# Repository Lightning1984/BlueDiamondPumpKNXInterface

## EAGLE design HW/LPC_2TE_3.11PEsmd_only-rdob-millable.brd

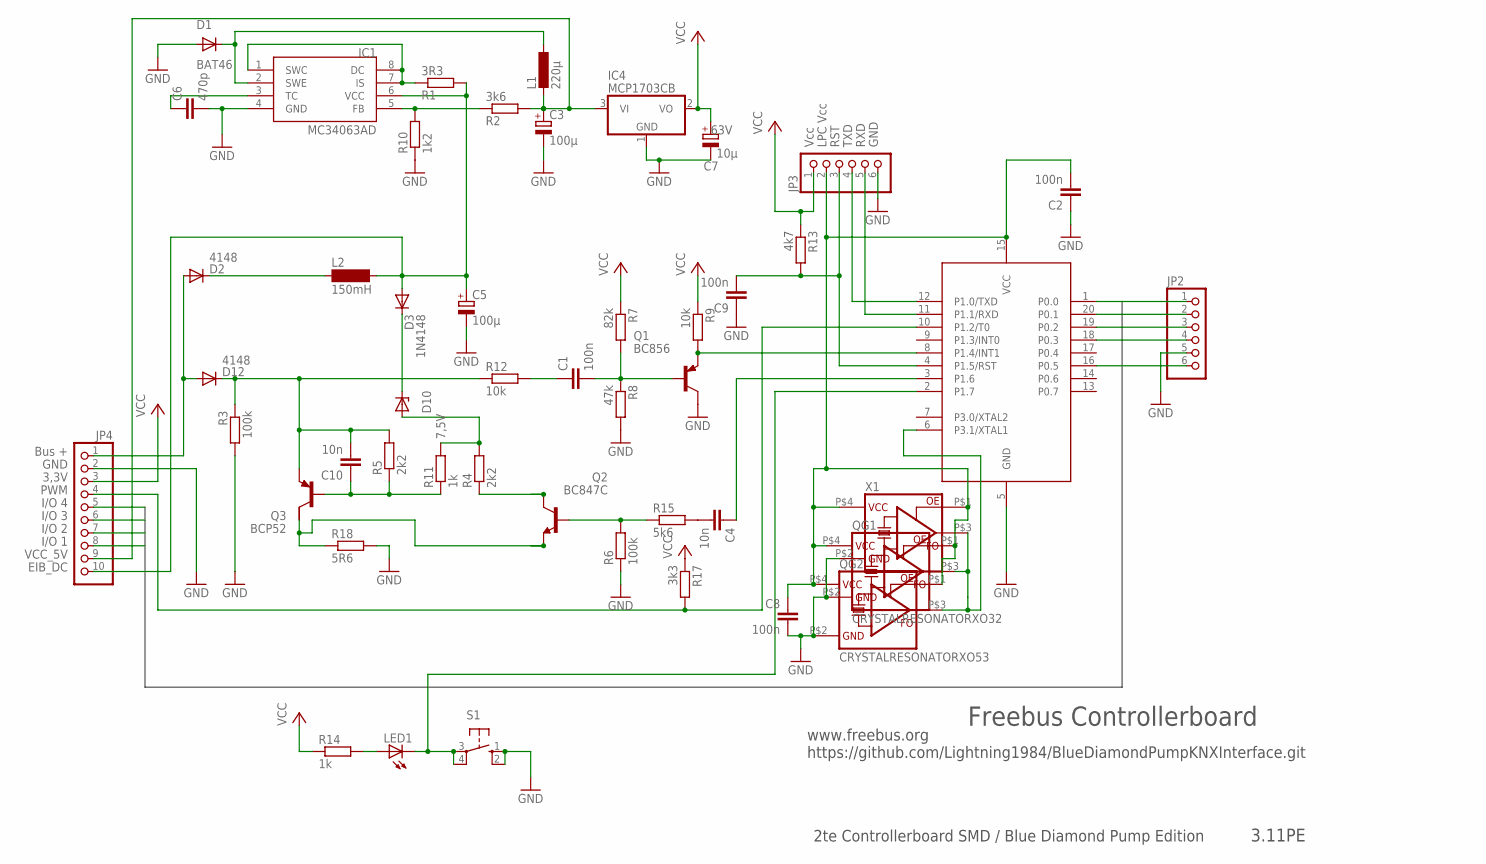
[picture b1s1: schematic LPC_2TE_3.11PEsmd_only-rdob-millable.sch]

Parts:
C1, C2, C8, C9: 100n; C0805K
C3: 100µ; E2,5-6
C4, C10: 10n; C0805K
C5: 100µ; E3,5-8
C6: 470p; C0805K
C7: 10µ; E2-5; VOLTAGE 63V
D1: BAT46; SOD-123
D2, D12: 4148; MINIMELF
D3: 1N4148; MINIMELF
D10: 7,5V; MINIMELF
IC1: MC34063AD; SOIC8
IC2: LPC922FDH; TSSOP20
IC4: MCP1703CB; SOT23
JP2: PINHD-1X06_2.54-0.70MM-DRILL; 1X06-0.70DRILL
JP3: PINHD-1X06_2.54-0.90MM-DRILL; 1X06-0.90DRILL
JP4: PINHD-1X10_2.54-S0.70MM-DRILL; 1X10-0.70DRILL
L1: 220µ; PIS28XX
L2: 150mH; BS11
LED1: LEDSMT1206; 1206
Q1: BC856; SOT23-BEC
Q2: BC847C; SOT23
Q3: BCP52; SOT223
QG1: CRYSTALRESONATORXO32; XO32
QG2: CRYSTALRESONATORXO53; XO53
R1: 3R3; R1206
R2: 3k6; R1206
R3, R6: 100k; R1206
R4, R5: 2k2; R1206
R7: 82k; R1206
R8: 47k; R1206
R9, R12: 10k; R1206
R10: 1k2; R1206
R11, R14: 1k; R1206
R13: 4k7; R1206
R15: 5k6; R1206
R17: 3k3; R1206
R18: 5R6; R1206
S1: 10-XX; B3F-10XX
X1: CRYSTALRESONATORXO91; XO91

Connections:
/RESET: C9.2, IC2.4 (P1.5/RST), JP3.3, R13.2
BASE: C1.2, Q1.B, R7.2, R8.1
BASE_SEND: Q2.1 (B), R6.2, R15.1
EIB+: D2.A, D12.A, JP4.1
EIB_DC: C5.+, D3.A, IC1.6 (VCC), JP4.10, L2.2, R1.2
FEEDBACK: IC1.5 (FB), R2.1, R10.2
GND: C2.1, C3.-, C5.-, C6.2, C7.-, C8.2, C9.1, D1.A, IC1.4 (GND), IC2.5 (GND), IC4.1 (GND), JP2.5, JP3.6, JP4.2, Q1.C, QG1.P$2 (GND), QG2.P$2 (GND), R3.2, R6.1, R8.2, R10.1, R18.2, S1.1 (S), S1.2 (S1), X1.P$2 (GND)
I_SENSE: Q2.2 (E), Q3.2 (C), R18.1
unnamed: Q2.3 (C), R4.1
unnamed: C10.2, D12.C, Q3.3 (E), R3.1, R5.2, R12.1
unnamed: IC2.6 (P3.1/XTAL1), QG1.P$3 (FO), QG2.P$3 (FO), X1.P$3 (FO)
unnamed: IC1.1 (SWC), IC1.7 (IS), IC1.8 (DC), R1.1
unnamed: LED1.A, R14.2
unnamed: D2.C, L2.1
unnamed: C6.1, IC1.3 (TC)
unnamed: D3.C, D10.C
unnamed: C1.1, R12.2
unnamed: C4.2, R15.2
unnamed: C10.1, Q3.1 (B), R5.1, R11.1
P0.0: IC2.1 (P0.0), JP2.1, JP4.8
P0.1: IC2.20 (P0.1), JP2.2, JP4.7
P0.2: IC2.19 (P0.2), JP2.3, JP4.6
P0.3: IC2.18 (P0.3), JP2.4, JP4.5
P0.5: IC2.16 (P0.5), JP2.6
PROG: IC2.2 (P1.7), LED1.C, S1.3, S1.4 (P1)
PWM: IC2.10 (P1.2/T0), JP4.4, R17.2
REFERENZ: D10.A, R4.2, R11.2
RXD: IC2.11 (P1.1/RXD), JP3.5
SIGIN: IC2.8 (P1.4/INT1), Q1.E, R9.2
SIGOUT: C4.1, IC2.3 (P1.6)
SWITCHED: D1.C, IC1.2 (SWE), L1.2 (1)
TXD: IC2.12 (P1.0/TXD), JP3.4
VCC: C7.+, IC4.2 (VO), JP3.1, JP4.3, R7.1, R9.1, R13.1, R14.1, R17.1
VCC_5V: C3.+, IC4.3 (VI), JP4.9, L1.1 (2), R2.2
VCC_LPC: C2.2, C8.1, IC2.15 (VCC), JP3.2, QG1.P$1 (OE), QG1.P$4 (VCC), QG2.P$1 (OE), QG2.P$4 (VCC), X1.P$1 (OE), X1.P$4 (VCC)

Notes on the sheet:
Bus +
GND
3,3V
PWM
I/O 1
I/O 2
I/O 3
I/O 4
Vcc
LPC Vcc
RST
TXD
RXD
VCC_5V
Freebus Controllerboard
www.freebus.org https://github.com/Lightning1984/BlueDiamondPumpKNXInterface.git
2te Controllerboard SMD / Blue Diamond Pump Edition
3.11PE
EIB_DC

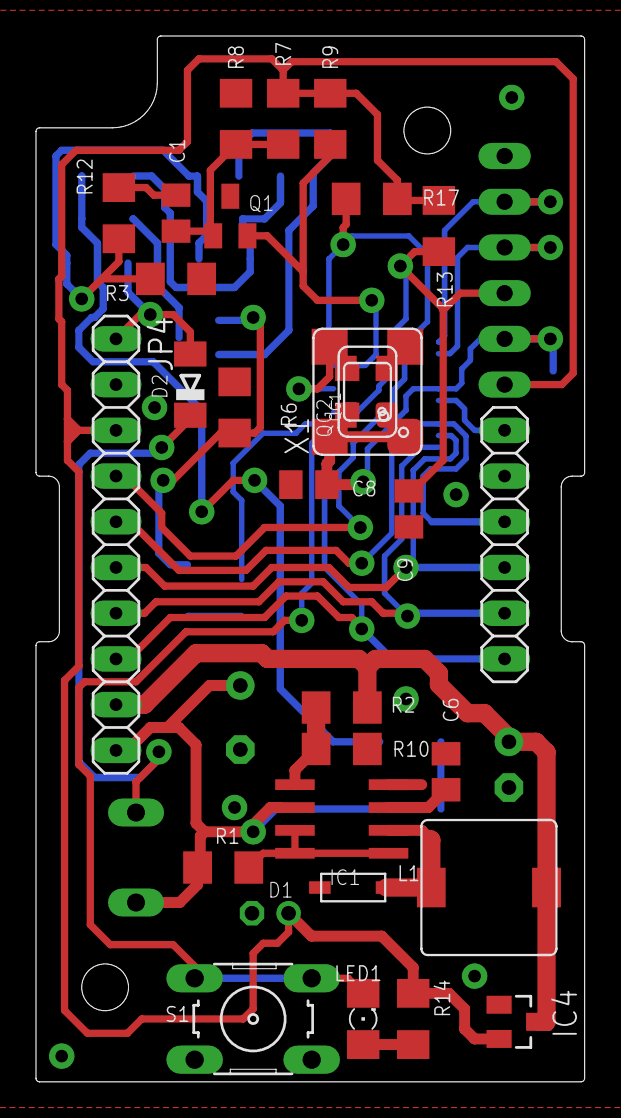
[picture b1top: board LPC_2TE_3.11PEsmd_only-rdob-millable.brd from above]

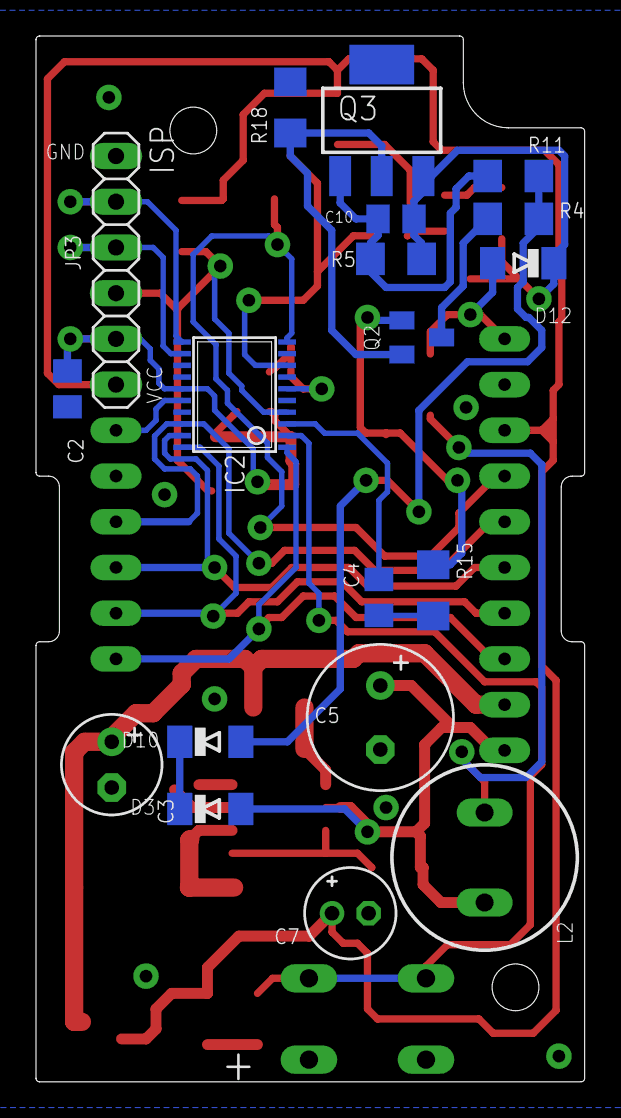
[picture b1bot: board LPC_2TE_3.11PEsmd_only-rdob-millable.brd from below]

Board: 2 copper layers, 30.5 x 58.1 mm, 48 parts (19 on the bottom side), 35 nets.

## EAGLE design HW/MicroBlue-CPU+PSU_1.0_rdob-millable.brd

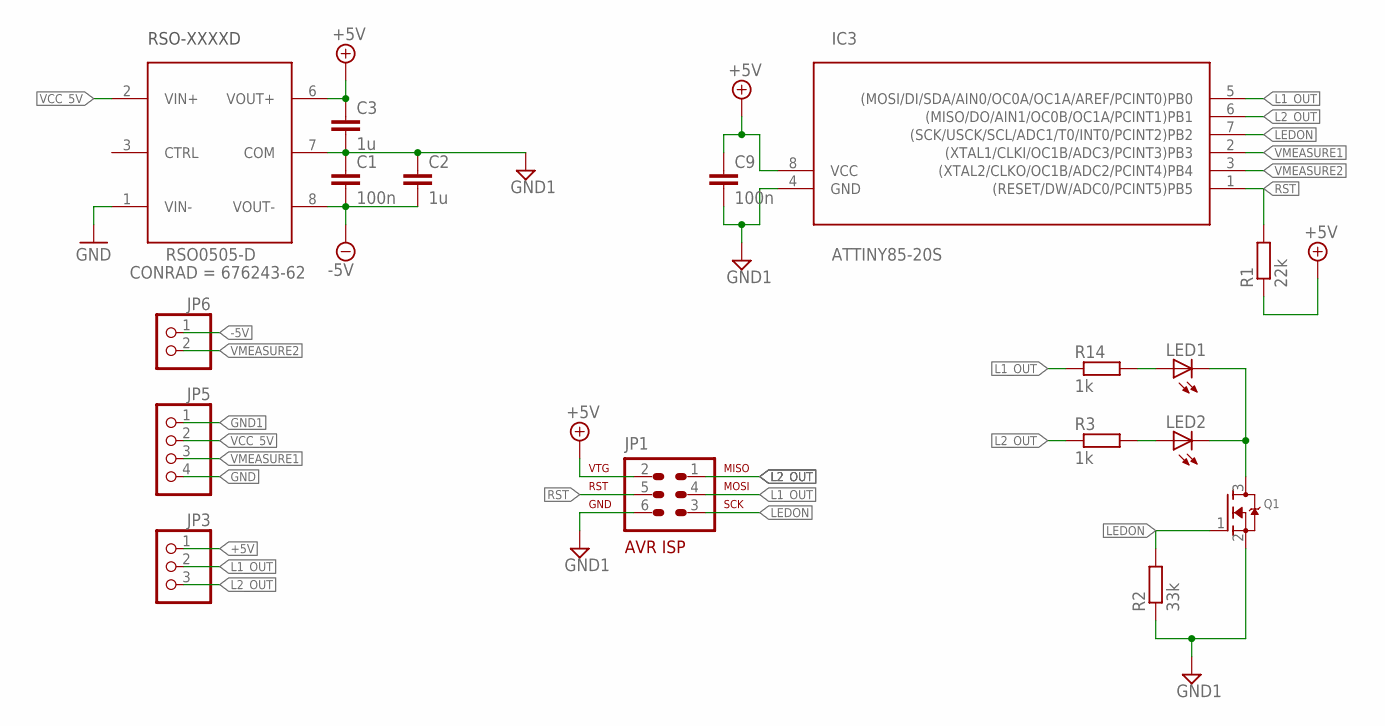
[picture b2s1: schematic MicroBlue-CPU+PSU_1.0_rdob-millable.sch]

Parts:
C1, C9: 100n; C0805K
C2, C3: 1u; C0805K
IC3: ATTINY85-20S; SOIC8
JP1: AVR-ISP-6R
JP3: PINHD-1X03_2.54-0.90MM-DRILL; 1X03-0.90DRILL
JP5: PINHD-1X04_2.54-0.90MM-DRILL; 1X04-0.90DRILL
JP6: PINHD-1X02_2.54-0.90MM-DRILL; 1X02-0.90DRILL
LED1, LED2: LEDSMT1206; 1206
Q1: MOSFET-NREFLOW; SOT23
R1: 22k; R1206
R2: 33k; R1206
R3, R14: 1k; R1206
RSO0505-D: RSO-0505D; RSO-XXXX

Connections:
+5V: C3.1, C9.1, IC3.8 (VCC), JP1.2, JP3.1, R1.1, RSO0505-D.6 (VOUT+)
-5V: C1.2, C2.2, JP6.1, RSO0505-D.8 (VOUT-)
GND: JP5.4, RSO0505-D.1 (VIN-)
GND1: C1.1, C2.1, C3.2, C9.2, IC3.4 (GND), JP1.6, JP5.1, Q1.2 (S), R2.1, RSO0505-D.7 (COM)
L1_OUT: IC3.5 ((MOSI/DI/SDA/AIN0/OC0A/OC1A/AREF/PCINT0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), JP1.4, JP3.2, R14.1
L2_OUT: IC3.6 ((MISO/DO/AIN1/OC0B/OC1A/PCINT1)PB1), JP1.1, JP3.3, R3.1
LEDON: IC3.7 ((SCK/USCK/SCL/ADC1/T0/INT0/PCINT2)PB2), JP1.3, Q1.1 (G), R2.2
unnamed: LED2.A, R3.2
unnamed: LED1.A, R14.2
PROG: LED1.C, LED2.C, Q1.3 (D)
RST: IC3.1 ((RESET/DW/ADC0/PCINT5)PB5), JP1.5, R1.2
VCC_5V: JP5.2, RSO0505-D.2 (VIN+)
VMEASURE1: IC3.2 ((XTAL1/CLKI/OC1B/ADC3/PCINT3)PB3), JP5.3
VMEASURE2: IC3.3 ((XTAL2/CLKO/OC1B/ADC2/PCINT4)PB4), JP6.2

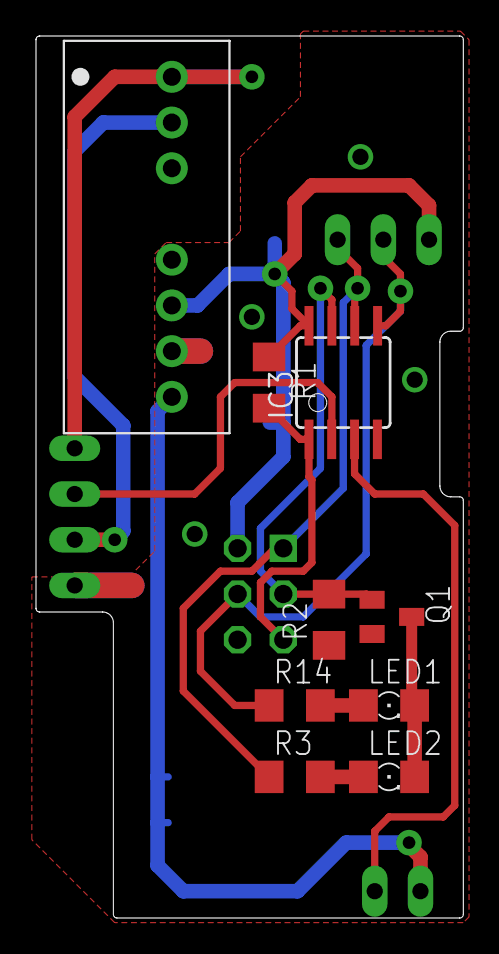
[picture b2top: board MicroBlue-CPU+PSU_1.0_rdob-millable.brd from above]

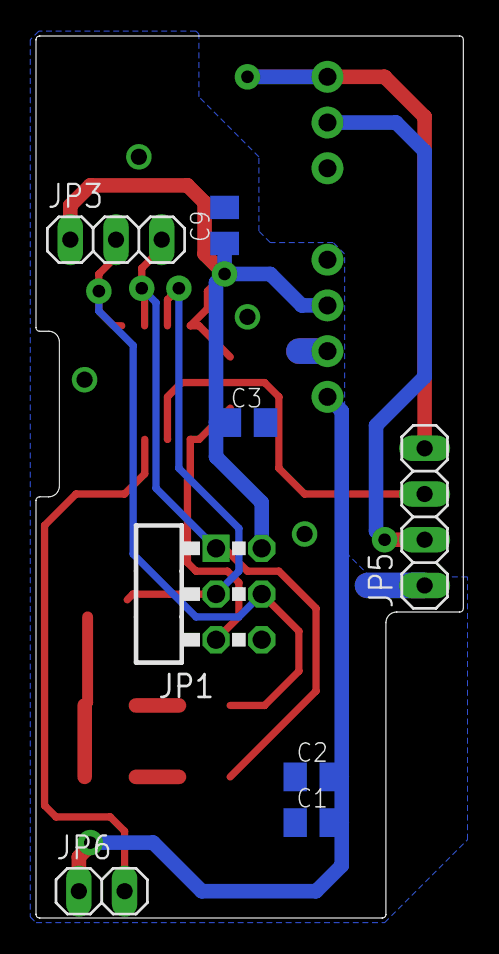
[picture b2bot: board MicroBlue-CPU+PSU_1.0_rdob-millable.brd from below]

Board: 2 copper layers, 23.7 x 49.0 mm, 17 parts (8 on the bottom side), 14 nets.

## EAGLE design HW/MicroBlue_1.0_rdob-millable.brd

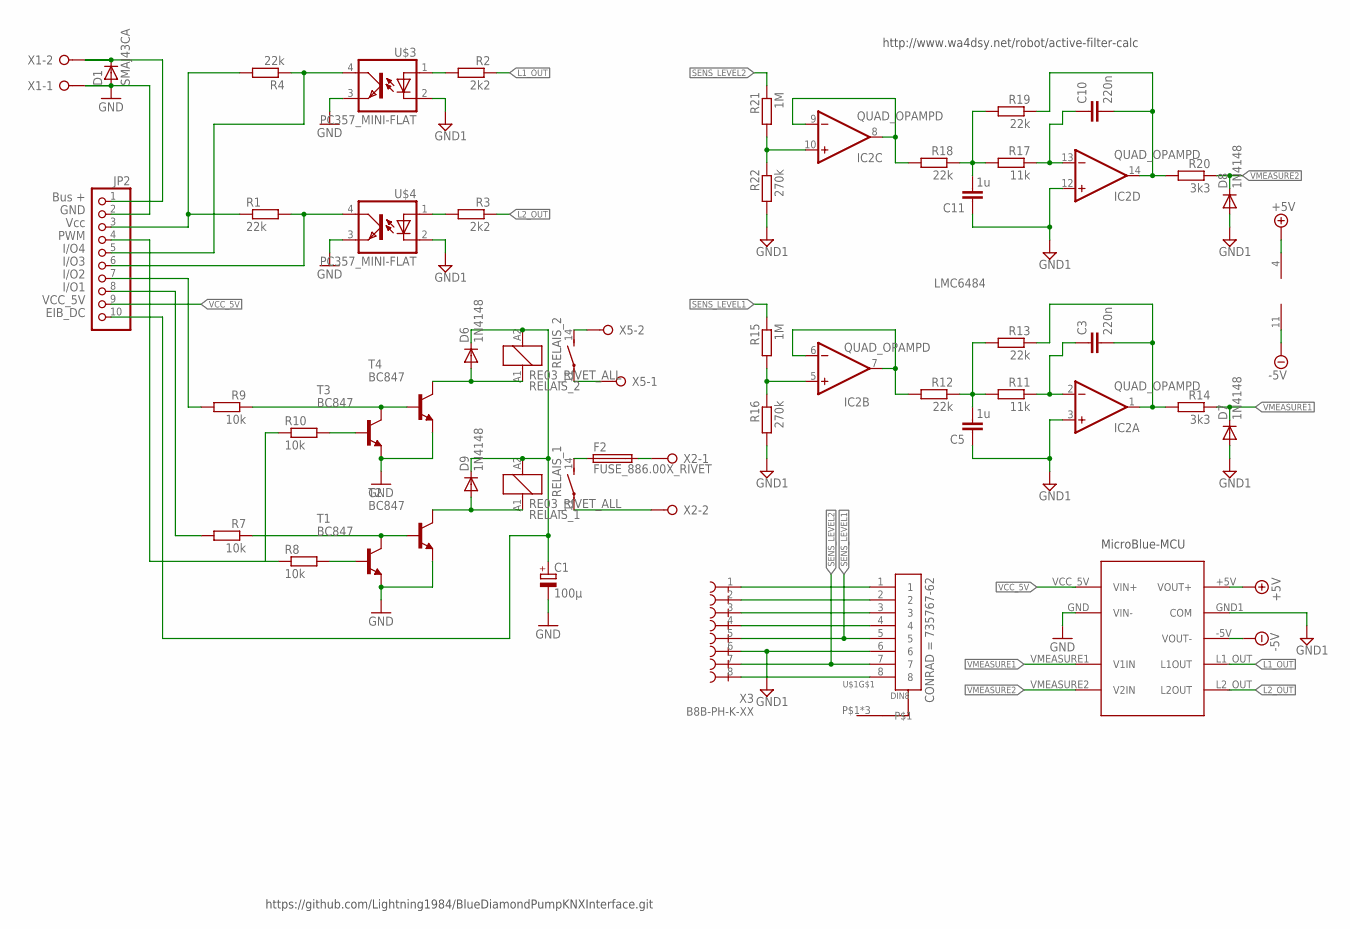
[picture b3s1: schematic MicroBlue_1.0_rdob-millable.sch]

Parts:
C1: 100µ; E3,5-8
C3, C10: 220n; C0805K
C5, C11: 1u; C0805K
D1: SMAJ43CA; SMB
D6, D7, D8, D9: 1N4148; MINIMELF
F2: FUSE_886.00X_RIVET; 886.00X_RIVET
IC2: QUAD_OPAMPD; SO14
JP2: PINHD-1X10_2.54-S0.90MM-DRILL; 1X10-0.90DRILL
R1, R4, R12, R13, R18, R19: 22k; M1206
R2, R3: 2k2; M1206
R7, R8, R9, R10: 10k; M1206
R11, R17: 11k; M1206
R14, R20: 3k3; M1206
R15, R21: 1M; M1206
R16, R22: 270k; M1206
RELAIS_1, RELAIS_2: RE03_RIVET_ALL; G5Q-SPST-RIVET-ALL
T1, T2, T3, T4: BC847; SOT23
U$1: DIN8
U$3, U$4: PC357_MINI-FLAT; PC357
U$5: MICROBLUE-MCU_V2; MICROBLUE-MCU-V2
X1: W237-02PNORMAL; W237-132
X2, X5: W237-02P_RIVET; W237-132-RIVET
X3: B8B-PH-K-XX

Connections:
+5V: IC2.4 (V+), U$5.+5V (VOUT+)
-5V: IC2.11 (V-), U$5.-5V (VOUT-)
EIB+: D1.1 (C), JP2.1, X1.2
EIB_DC: C1.+, D6.C, D9.C, JP2.10, RELAIS_1.A2 (2), RELAIS_2.A2 (2)
GND: C1.-, D1.2 (A), JP2.2, T1.2 (E), T2.2 (E), T3.2 (E), T4.2 (E), U$3.3 (EMIT), U$4.3 (EMIT), U$5.GND (VIN-), X1.1
GND1: C5.1, C11.1, D7.A, D8.A, IC2.3 (+IN), IC2.12 (+IN), R16.2, R22.2, U$1.6, U$3.2 (C), U$4.2 (C), U$5.GND1 (COM), X3.6
IO1: JP2.7, R9.2
IO2: JP2.8, R7.2
IO3: JP2.6, R1.2, U$4.4 (COL)
IO4: JP2.5, R4.1, U$3.4 (COL)
L1_OUT: R2.1, U$5.L1_OUT (L1OUT)
L2_OUT: R3.1, U$5.L2_OUT (L2OUT)
unnamed: U$1.1, X3.1
unnamed: RELAIS_1.11, X2.2
unnamed: U$1.2, X3.2
unnamed: U$1.4, X3.4
unnamed: U$1.3, X3.3
unnamed: F2.1, RELAIS_1.14 (S)
unnamed: U$1.8, X3.8
unnamed: RELAIS_2.14 (S), X5.2
unnamed: RELAIS_2.11, X5.1
unnamed: F2.2, X2.1
unnamed: C5.2, R11.2, R12.1, R13.2
unnamed: R2.2, U$3.1 (A)
unnamed: R3.2, U$4.1 (A)
unnamed: R7.1, T1.3 (C), T2.1 (B)
unnamed: C3.2, IC2.1 (OUT), R13.1, R14.2
unnamed: R9.1, T3.3 (C), T4.1 (B)
unnamed: D6.A, RELAIS_2.A1 (1), T4.3 (C)
unnamed: R8.2, T1.1 (B)
unnamed: R10.2, T3.1 (B)
unnamed: C3.1, IC2.2 (-IN), R11.1
unnamed: IC2.6 (-IN), IC2.7 (OUT), R12.2
unnamed: IC2.5 (+IN), R15.2, R16.1
unnamed: C11.2, R17.2, R18.1, R19.2
unnamed: C10.2, IC2.14 (OUT), R19.1, R20.2
unnamed: C10.1, IC2.13 (-IN), R17.1
unnamed: IC2.8 (OUT), IC2.9 (-IN), R18.2
unnamed: IC2.10 (+IN), R21.2, R22.1
PWM: JP2.4, R8.1, R10.1
R3: D9.A, RELAIS_1.A1 (1), T2.3 (C)
SENS_LEVEL1: R15.1, U$1.5, X3.5
SENS_LEVEL2: R21.1, U$1.7, X3.7
VCC: JP2.3, R1.1, R4.2
VCC_5V: JP2.9, U$5.VCC_5V (VIN+)
VMEASURE1: D7.C, R14.1, U$5.VMEASURE1 (V1IN)
VMEASURE2: D8.C, R20.1, U$5.VMEASURE2 (V2IN)

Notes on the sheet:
Bus +
GND
Vcc
PWM
I/O4
I/O3
I/O2
I/O1
http://www.wa4dsy.net/robot/active-filter-calc
EIB_DC
VCC_5V
https://github.com/Lightning1984/BlueDiamondPumpKNXInterface.git

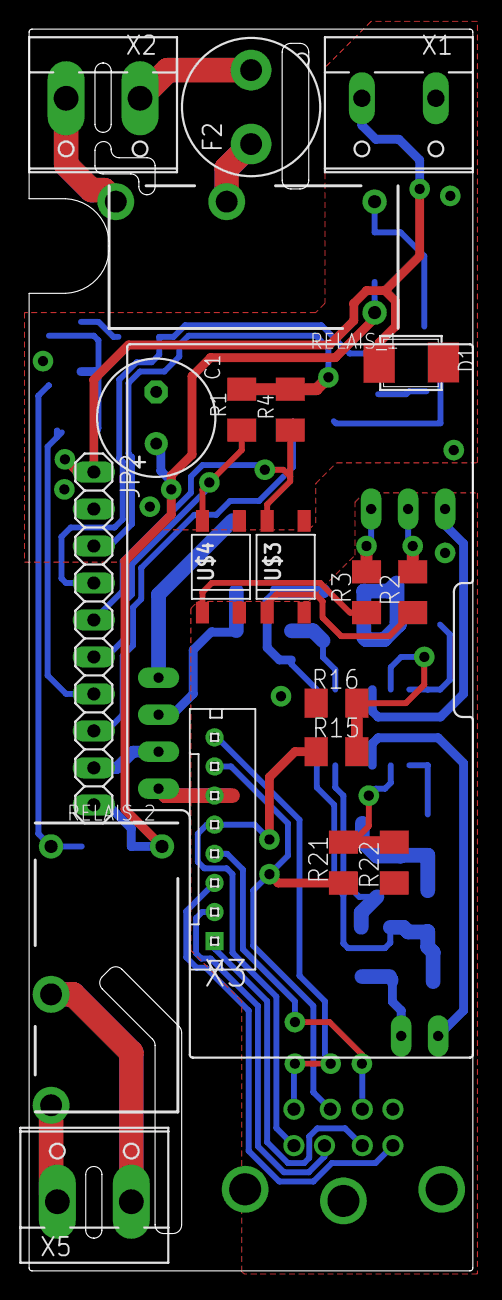
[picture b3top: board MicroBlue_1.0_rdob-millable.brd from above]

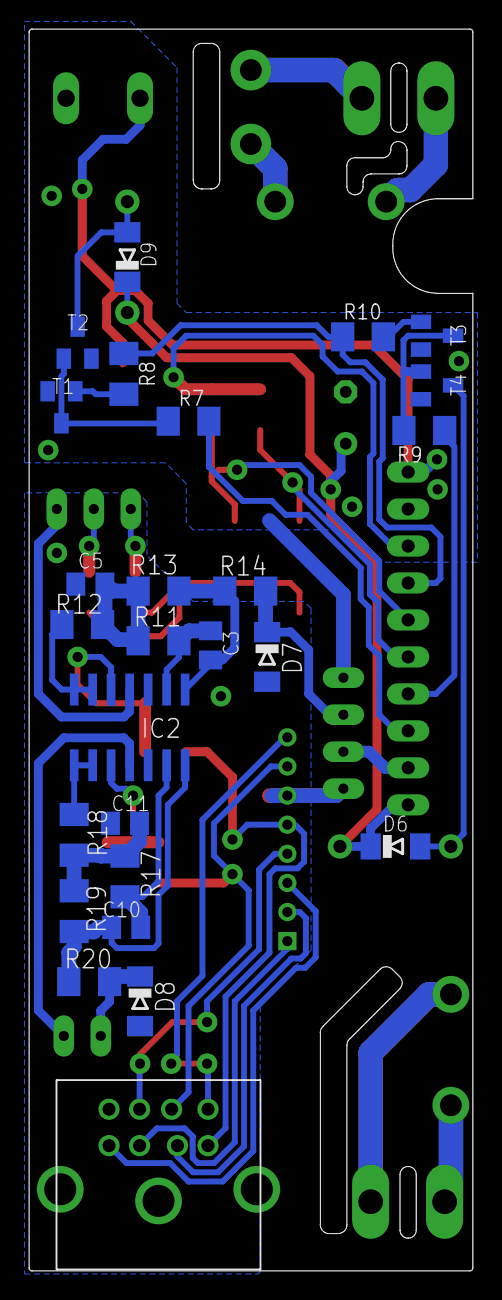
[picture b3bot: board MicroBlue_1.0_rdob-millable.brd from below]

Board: 2 copper layers, 30.5 x 85.3 mm, 47 parts (25 on the bottom side), 47 nets.

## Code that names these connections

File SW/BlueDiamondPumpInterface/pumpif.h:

/**
 * @file
 * @Author Rupert Dobrounig (rupert.dobrounig@gmail.com)
 * @date   September, 2016
 * @brief  Header File for the MicroBlue Pump KNX Interface controller
 * @version 1.0
 * @mainpage
 * @section intro_sec Introduction
 * Blue Diamond MicroBlue Condensate Pump KNX Interface
 * implemented as finite state machine
 * @section descript_sec Detailed description
 * This hardware / software allows to directly integrate a Blue Diamond MicroBlue (Other Blue Diamond pumps might work as well, but untested)
 * \n into a KNX bus for monitoring, alarming and power saving purposes!
 * \n There are 2 independent relais outputs, one of them is internally fused (to be used for the pump), the second one can be used to turn off the AC unit in case of a pump issue.
 * \n The system is galvanically isolated between the Pump and the KNX bus using a RSO0505-D DCDC converter and optocouplers
 * \n Due to the design the system draws ~18mA from the Bus with both Relais switched on
 * \n This does not comply with the KNX max allowed consumption of 12mA, therefore be warned if your KNX Power supply is already close to its limits.
 * @section credit_sec Credits
 * The System fits into a 2TE REG housing and is mostly built on a modified version of the Selfbus 2TE Controller with LPC922 and the "Kombi Aktor 2In 2Out fuer 2TE" 
 * \n as LPC922 firmware Version 1.0b can be used
 * @see http://selfbus.myxwiki.org/xwiki/bin/view/Technik/Controller_922_2TE
 * @see http://selfbus.myxwiki.org/xwiki/bin/view/Ger%C3%A4te/Ausg%C3%A4nge/2in2out_2TE
 * @see https://github.com/selfbus/software/raw/master/2in2out/Releases/2in2out_1.0b.hex
 * @section download_sec Download
 * @see https://github.com/Lightning1984/BlueDiamondPumpKNXInterface
 * @see https://drive.google.com/drive/folders/0B65eQ9bjsU6ZTXUzSnhiRGNyeTA?usp=sharing
 * @copyright (C) 2016 Rupert Dobrounig, Creative Commons Attribution-NonCommercial-ShareAlike 4.0 International
 * 
 */
#ifndef PUMPIF_H_
#define PUMPIF_H_


/** @name PIN Definitions
 @{**/
#define OUTPORT PORTB	//The Port everything is connected to
#define OUT1 PB1		//Output Channel 1 - Blue LED - Pump ON
#define OUT2 PB0		//Output Channel 2 - Red LED - Alarm
#define LEDON PB2		//LED Enable
#define ANALOG1 PB3		//Analog Voltage Input 1 - Normal (Pump ON) Water Level
#define ANALOG2	PB4		//Analog Voltage Input 2 - Alarm Water Level
#define BANDGAP 253		//Used to switch to Bandgap ADC in
#define QUERY 255		//Used to query the current Muxer settings
/** @}*/

/** @name ADC Buffer value Definitions
 @{**/
#define CHAN1_BUFFER_SIZE 8 // Channel 1 buffer size, 2^n values
#define CHAN1_BUFFER_MASK (CHAN1_BUFFER_SIZE - 1) // buffer mask, used for modulo arithmetic
#define CHAN2_BUFFER_SIZE 8 // Channel 2 buffer size, 2^n values
#define CHAN2_BUFFER_MASK (CHAN2_BUFFER_SIZE - 1) // buffer mask, used for modulo arithmetic
#define BUFFER_FAIL     0
#define BUFFER_SUCCESS  1
/** @}*/

/** @name ADC Measurement value Definitions
 @{**/
#define PUMPONVAL		575		//Pump switch on hysteresis value
#define PUMPOFFVAL		610		//Pump switch off hysteresis value
#define PUMPPWRDOWN		200		//Pump power switched off low value
#define ALARMONVAL		585		//Alarm switch on hysteresis value
#define ALARMOFFVAL		620		//Alarm switch off hysteresis value
#define ALARMPWRDOWN	200		//Alarm power switched off low value
/** @}*/

/** @name Status Flag Definitions
 @{**/
#define STATUSADCVALUEAVAILABLE 0
/** @}*/

/** @name State Flag Definitions
 @{**/
#define STATEPOWEROFF 0
#define STATETRAINING 1
#define STATEIDLE 2
#define STATEPUMPING 3
#define STATEALARM 4
/** @}*/

/** @name Other Defines
 @{**/
#define TRAININGTOUT 16000	//Training Time Out in ms
#define DEBUGLED			//Set this define to enable the debug LEDs, needs more power
/** @}*/

/** @brief average Data memory
 *
 *  structure to hold the average values calculated
 **/
typedef volatile struct avgdata avgdata;
struct avgdata {
	uint16_t chan1last2avg;
	uint16_t chan2last2avg;
	uint16_t chan1first4avg;
	uint16_t chan2first4avg;
};
/**
* @brief    get milliseconds since system started, will overflow every ~49 Days
* @return	Milliseconds.
*/
uint32_t millis();
/**
 @brief			Function to write into the overwriting Channel1 ringbuffer 
 @param[in]		data	the new value to store in the ringbuffer
 @return		whether buffer write was successful or not
 @retval		BUFFER_SUCCESS
 @retval		BUFFER_FAIL
*/
uint8_t Chan1BufferIn(uint16_t data);
/**
 @brief			Function to read data from Channel1 ringbuffer 
 @param[in]		buffer index to return, -7 to 0, more negative means older data
 @return		the requested data
*/
uint16_t Chan1BufferOut(int8_t position);
/**
 @brief			Function to write into the overwriting Channel2 ringbuffer 
 @param[in]		data	the new value to store in the ringbuffer
 @return		whether buffer write was successful or not
 @retval		BUFFER_SUCCESS
 @retval		BUFFER_FAIL
*/
uint8_t Chan2BufferIn(uint16_t data);
/**
 @brief			Function to read data from Channel2 ringbuffer 
 @param[in]		buffer index to return, -7 to 0, more negative means older data
 @return		the requested data
*/
uint16_t Chan2BufferOut(int8_t position);
/**
 @brief			Function to set or get the current ADC Mux Settings 
 @param[in]		channel	the channel to switch the Muxer to or QUERY to return the current setting
 @arg			ANALOG1
 @arg			ANALOG2
 @arg			BANDGAP
 @arg			QUERY
 @return		The Current Muxer channel
 @retval		ANALOG1
 @retval		ANALOG2
 @retval		BANDGAP
*/
uint8_t MuxChannel(uint8_t channel);
/**
 @brief			Function to calculate average values from the Buffer
 @param[in]		p_mydata Where to save the calculated average values
 @return		none
*/
void ProcessData(avgdata * p_mydata);
/**
 @brief			Callback function pointer to FSM state functions
 @param[in]		stateflags the stateflags
 @return		none
*/
void (*statehandler) (uint8_t * stateflags);
/**
 @brief			FSM state functions for state: Poweroff
 @param[in]		stateflags the stateflags
 @return		none
*/
void state_pwroff(uint8_t * stateflags);
/**
 @brief			FSM state functions for state: Training
 @param[in]		stateflags the stateflags
 @return		none
*/
void state_training(uint8_t * stateflags);
/**
 @brief			FSM state functions for state: Idle
 @param[in]		stateflags the stateflags
 @return		none
*/
void state_idle(uint8_t * stateflags);
/**
 @brief			FSM state functions for state: Pumping
 @param[in]		stateflags the stateflags
 @return		none
*/
void state_pumping(uint8_t * stateflags);
/**
 @brief			FSM state functions for state: Alarm
 @param[in]		stateflags the stateflags
 @return		none
*/
void state_alarm(uint8_t * stateflags);

#endif /* PUMPIF_H_ */

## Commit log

2016-12-16 Inital Commit
2016-12-16 Some Initial Corrections
